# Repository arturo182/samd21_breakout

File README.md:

# Atmel/Microchip SAM D21 breakout board aka. SAMinator

A SAM D21 breakout board designed to fit into a USB connector.

Never got it printed in 2.2mm, but tested and worked in 1.6mm with some back support.

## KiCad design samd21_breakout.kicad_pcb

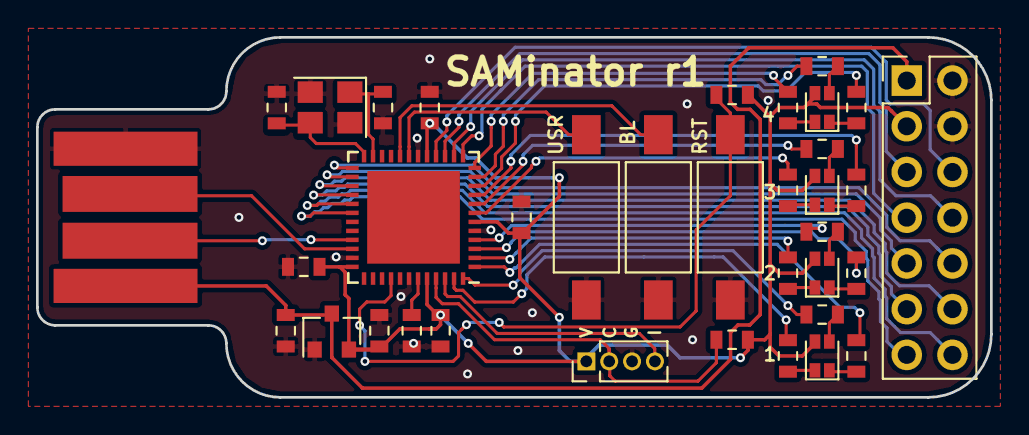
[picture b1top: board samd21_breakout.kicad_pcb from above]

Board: 2 copper layers, 53.0 x 20.0 mm, 36 parts (0 on the bottom side), 47 nets.

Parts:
C1, C2, C3, C4: 0.1uF; C_0603_1608Metric
C5, C8, C9: 1uF; C_0603_1608Metric
C6, C7: 12pF; C_0603_1608Metric
D1, D2, D3, D4: LED_GRAB; LED_0606_RGBA
J1: USB_A; usb-PCB
J2: SWD; PinHeader_1x04_P1.27mm_Vertical
J3: Conn_02x07_Odd_Even; PinHeader_2x07_P2.54mm_Vertical
R1: 10K; R_0603_1608Metric
R2: 1K; R_0603_1608Metric
R3, R4, R5, R6, R7, R8, R9, R10, R11, R12, R13, R14: 360R; R_0603_1608Metric
SW1: RESET; SW_SPST_FSMSM
SW2: BOOTL; SW_SPST_FSMSM
SW3: USR; SW_SPST_FSMSM
U1: ATSAMD21G16A; QFN-48-1EP_7x7mm_P0.5mm_EP5.15x5.15mm
U2: XC6206P332MR; SOT-23
Y1: 16MHz; Crystal_SMD_3225-4Pin_3.2x2.5mm

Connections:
+3V3: C1.1, C2.1, C3.1, C4.1, C9.1, D1.3, D2.3, D3.3, D4.3, J2.1, J3.3, R1.1, R2.1, U1.6, U1.17, U1.36, U1.44, U2.2
/BTN_BOOT: SW2.2, U1.20
/BTN_USR: SW3.2, U1.19
/LED1_B: R5.2, U1.48
/LED1_G: R3.2, U1.1
/LED1_R: R4.2, U1.47
/LED2_B: R8.2, U1.4
/LED2_G: R6.2, U1.3
/LED2_R: R7.2, U1.2
/LED3_B: R11.2, U1.8
/LED3_G: R9.2, U1.9
/LED3_R: R10.2, U1.7
/LED4_B: R14.2, U1.11
/LED4_G: R12.2, U1.10
/LED4_R: R13.2, U1.12
/PA8: J3.7, U1.13
/PA9: J3.8, U1.14
/PA10: J3.5, U1.15
/PA11: J3.6, U1.16
/PA16: J3.10, U1.25
/PA17: J3.9, U1.26
/PA18: J3.12, U1.27
/PA19: J3.11, U1.28
/PA20: J3.14, U1.29
/PA21: J3.13, U1.30
/RESET: R1.2, SW1.2, U1.40
/SWDCLK: J2.2, R2.2, U1.45
/SWDIO: J2.4, U1.46
/USB_D+: J1.3, U1.34
/USB_D-: J1.2, U1.33
GND: C1.2, C2.2, C3.2, C4.2, C5.2, C6.2, C7.2, C8.1, C9.2, J1.4, J2.3, J3.2, J3.4, SW1.1, SW2.1, SW3.1, U1.5, U1.18, U1.35, U1.42, U2.1, Y1.2, Y1.4
unnamed: C5.1, U1.43
unnamed: C6.1, U1.23, Y1.1
unnamed: C7.1, U1.24, Y1.3
unnamed: D1.1, R3.1
unnamed: D1.2, R4.1
unnamed: D1.4, R5.1
unnamed: D2.1, R6.1
unnamed: D2.2, R7.1
unnamed: D2.4, R8.1
unnamed: D3.1, R9.1
unnamed: D3.2, R10.1
unnamed: D3.4, R11.1
unnamed: D4.1, R12.1
unnamed: D4.2, R13.1
unnamed: D4.4, R14.1
VBUS: C8.2, J1.1, J3.1, U2.3

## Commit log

2018-02-11 Initial import
2019-05-11 Add readme, images, schematic, and update the USB symbol
